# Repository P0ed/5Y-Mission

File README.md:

# 5Y-Mission
4U modular analog synthesizer

The panel contains 4 submodules with identical UI. Each unit has:  
* 8 banana jacks and 4 potentiometers laid out in a 4x3 grid  
* 2 5mm LED  
* 2 toggle switches  

### Parts:  
Potentiometer: Bourns 51AAD-B24-A20L  
Banana jack: Pomona 1581  
Switch: NKK A12HP  
Opamp: AD823  
Electronic switch: ADG419/DG419  
Multiplier: AD633  
Zener reference: ADR5045/LM4040  
Flip-flop: CD4013  
NAND: CD4093  
XOR: CD4070  
Counter: CD4029  
VCA: THAT2180  

Resistors SMT: Panasonic 0.1-1% 1206 E6  
Capacitors SMT: TDK C0G 50V 1206 E6  
Resistors THT: Vishay MBA0204 1% 0.4W E6  
Capacitors THT: TDK C0G 50V P:5mm E6  

Board connectors:  
Power: MTA156  
Signal male: 1-826629-6 female:  1-215297-6  

Case connectors:  
Power: AG4MCC  
Audio: AG3MCC  
Controls: AG5MCC  

LEMO connectors:  
FGG.0B.303.CLAD42  
EGG.0B.303.CLL  
PHG.0B.303.CLLD42  

### OSHWLab:
* [PCB panel](https://oshwlab.com/com.poed/panel-typ-i)
* [Dual modules motherboard PCB](https://oshwlab.com/com.poed/motherboard)
* [Mixer module](https://oshwlab.com/com.poed/4u-mixer)
* [Blank module PCB](https://oshwlab.com/com.poed/blank)

### Modules:
* [Voltage mixer](Modules/Mixer.md)
* [4 step sequencer](Modules/Sequencer.md)
* [Function generator](Modules/Function.md)
* AD633 multiplier

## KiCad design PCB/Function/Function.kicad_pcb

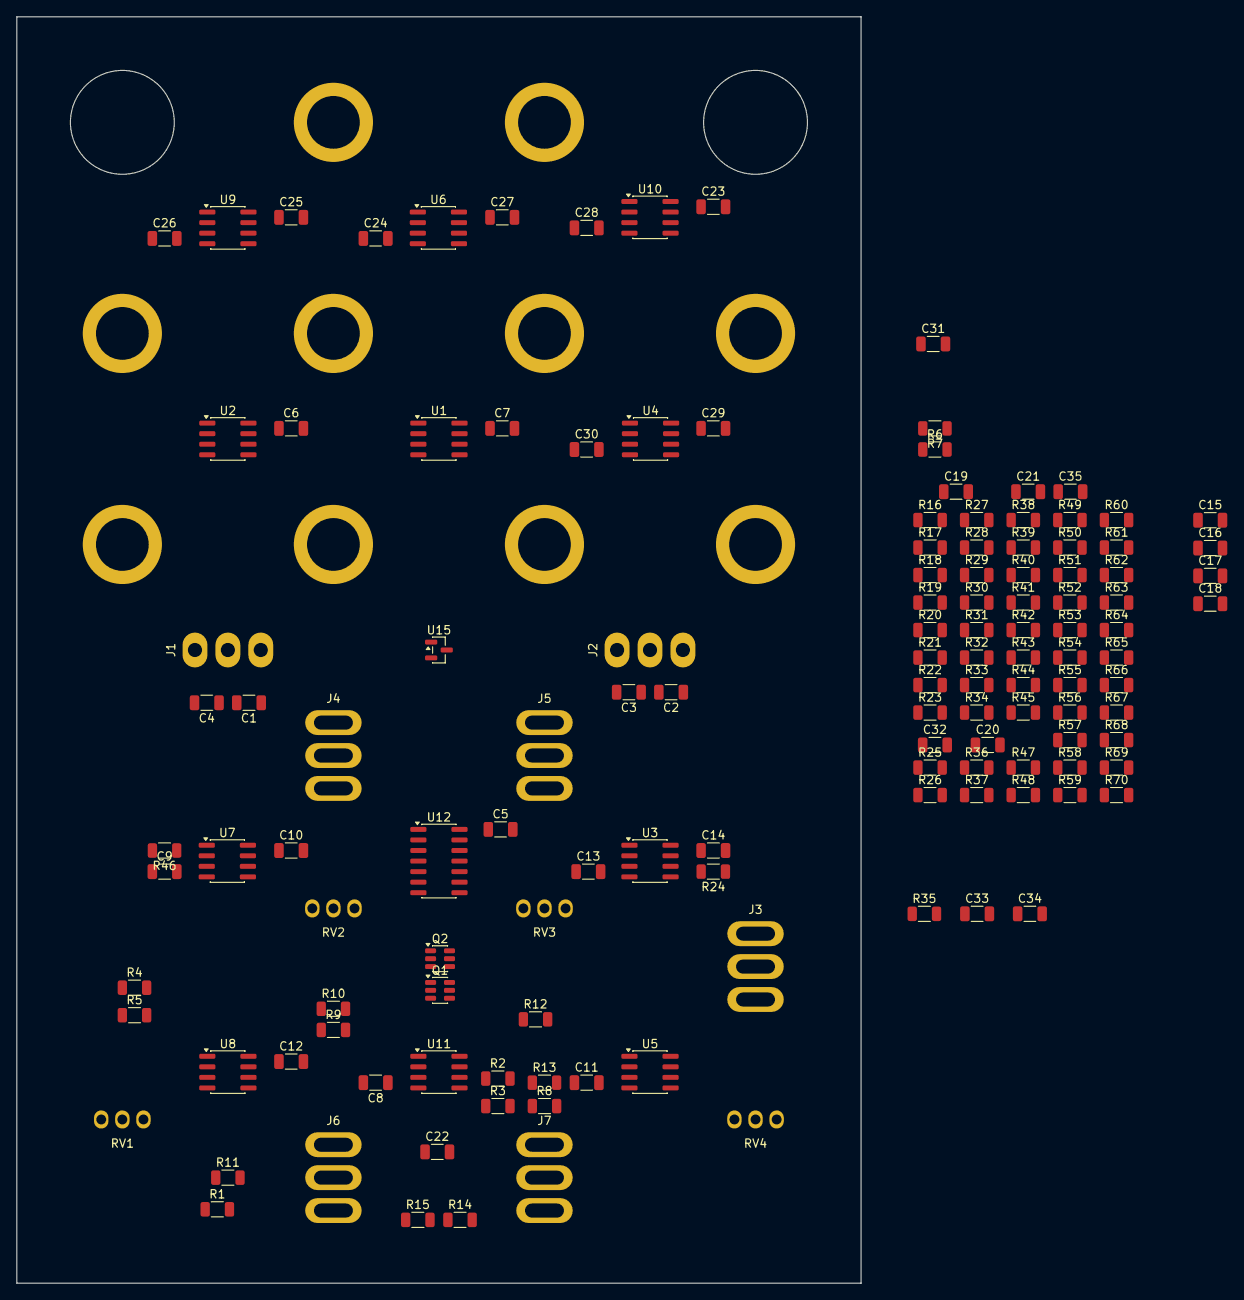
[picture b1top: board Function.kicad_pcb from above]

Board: 2 copper layers, 101.6 x 152.4 mm, 141 parts (0 on the bottom side), 75 nets, no tracks yet.

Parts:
C1, C2, C3, C4: 4u7; C_1206_3216Metric
C5, C6, C7, C8, C9, C10, C11, C12, C13, C14, C15, C16, C17, C23, C24, C25, C26, C27, C28, C29, C30: 100n; C_1206_3216Metric
C18, C19, C20, C21, C31, C32, C33, C34, C35: 47p; C_1206_3216Metric
C22: 4n7; C_1206_3216Metric
J1: MTA156-3
J2: MTA156-3-PWR; MTA156-3
J3, J4, J5: MN12; MBNF15
J6, J7: MBNF15
J**1, J**2, J**3, J**4, J**5, J**6, J**7, J**8, J**9, J**10: Pomona_1581; Pomona-1581
Q1: BC847; SOT-23-6
Q2: BCM857; SOT-23-6
R1, R12, R14, R15, R16, R47, R49: 4K7; R_1206_3216Metric
R2, R8, R56: 680K; R_1206_3216Metric
R3, R5, R45, R55: 10K; R_1206_3216Metric
R4, R6, R7, R9, R11, R22, R25, R50, R51, R52, R53, R54, R57, R58, R60, R63, R66, R69: 100K; R_1206_3216Metric
R10, R42, R44, R46, R48, R59, R61, R62, R64, R65, R67, R68, R70: 68K; R_1206_3216Metric
R13, R17, R39, R40: 150K; R_1206_3216Metric
R18: 6M8; R_1206_3216Metric
R19, R21, R24, R27, R29, R30, R31, R32, R34, R35, R36, R37: 47K; R_1206_3216Metric
R20, R28, R33, R38: 470; R_1206_3216Metric
R23, R26, R41, R43: 33K; R_1206_3216Metric
RV1, RV2, RV3, RV4: Bourns_51
U1, U2, U3, U4, U5, U6, U7, U8, U9, U10: AD823; SOIC-8
U11: ADG419; SOIC-8_3.9x4.9mm_P1.27mm
U12: 4013; SOIC-14_3.9x8.7mm_P1.27mm
U15: ADR5045; SOT-23

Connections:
ATK: R9.2, R51.2, U12.1 (Q)
DEK: R52.2, U12.13 (Q)
DRV: C31.2, R44.1, R50.1, U8.1
END: J3.1, R11.1, R22.1, U2.1
ENDO: J**2.1, R19.2, R20.1
FAB: J4.2, U10.6 (-), U10.7
FALLN: J4.1, R66.2
FALLP: J4.3, R69.2
FALL_IN: J**8.1, RV3.3
FAP: R14.1, U10.5 (+)
FB: R70.2, U10.1, U10.2 (-)
FP: RV1.2, U10.3 (+)
FREQ: J**7.1, R62.2, R68.2
GND: C1.2, C2.2, C3.1, C4.1, C5.2, C6.2, C7.2, C8.2, C9.1, C10.2, C11.1, C12.2, C13.1, C14.2, C15.1, C16.2, C17.1, C23.2, C24.1, C25.2, C26.1, C27.2, C28.1, C29.2, C30.1, J1.2, J2.2, Q1.2 (B), Q1.6 (C), Q2.2 (B), Q2.6 (C), R1.1, R4.1, R6.2, R8.1, R10.2, R17.1, R23.1, R26.1, R31.1, R34.1, R36.1, R39.1, R40.1, R42.1, R53.2, R54.2, R58.1, RV1.1, RV2.1, RV3.1, RV4.1, U1.4 (V-), U2.4 (V-), U5.5 (+), U6.3 (+), U6.5 (+), U7.3 (+), U7.5 (+), U11.3 (GND), U12.3 (C), U12.4 (R), U12.6 (S), U12.7 (VSS), U12.8 (S), U12.9 (D), U12.11 (C), U15.2 (A)
HOLD: R56.1, U8.7, U11.6
HOLD_IN: J**10.1, R54.1, R55.2
LIM: R13.1, R25.1, U2.7
LIMO: J**5.1, R27.2, R28.1
LP: C22.2, R12.2, R21.1, R24.1, R29.1, R35.1, R43.2, U1.5 (+), U2.2 (-), U5.7
LPO: J**1.1, R37.2, R38.1
NLPO: J**4.1, R32.2, R33.1
NVFF: C32.2, R46.1, R65.2, U7.1
NVRF: C35.2, Q1.5 (B), R49.1, U6.1
unnamed: C18.2, R20.2, U3.1
unnamed: C19.2, R28.2, U3.7
unnamed: C20.2, R33.2, U4.7
unnamed: C21.2, R38.2, U4.1
unnamed: R1.2, U1.6 (-)
unnamed: Q1.1 (E), Q1.4 (E), Q2.1 (E), Q2.4 (E), R45.1
unnamed: Q1.3 (C), Q2.3 (C), U11.1
unnamed: R14.2, RV3.2
unnamed: R15.2, RV4.2
unnamed: R45.2, U5.1
unnamed: R2.1, R3.2, U1.3 (+)
unnamed: R6.1, R7.2, U1.2 (-)
unnamed: R9.1, R10.1, R11.2, R18.2, U2.3 (+)
unnamed: R16.1, R17.2, U2.5 (+)
unnamed: R12.1, R13.2, U2.6 (-)
unnamed: R22.2, R23.2, R40.2, U3.3 (+)
unnamed: C18.1, R19.1, R21.2, U3.2 (-)
unnamed: R25.2, R26.2, R39.2, U3.5 (+)
unnamed: C19.1, R24.2, R27.1, U3.6 (-)
unnamed: R35.2, R36.2, U4.3 (+)
unnamed: C21.1, R34.2, R37.1, U4.2 (-)
unnamed: R30.2, R31.2, U4.5 (+)
unnamed: C20.1, R29.2, R32.1, U4.6 (-)
unnamed: R43.1, R44.2, U5.3 (+)
unnamed: R41.1, R42.2, U5.2 (-)
unnamed: C22.1, U5.6 (-), U11.2
unnamed: C35.1, R49.2, R59.1, R60.1, R61.1, U6.2 (-)
unnamed: C34.1, R48.2, R62.1, R63.1, R64.1, U6.6 (-)
unnamed: C32.1, R46.2, R66.1, R67.1, U7.2 (-)
unnamed: C33.1, R47.2, R65.1, R68.1, R69.1, R70.1, U7.6 (-)
unnamed: R52.1, R53.1, U8.3 (+)
unnamed: C31.1, R50.2, R51.1, U8.2 (-)
unnamed: R55.1, R56.2, U8.5 (+)
unnamed: R57.1, R58.2, U8.6 (-)
RAB: J5.2, U9.1, U9.2 (-)
RAP: R15.1, U9.3 (+)
RB: R64.2, U9.6 (-), U9.7
REF: J6.1, J7.1, R5.1, R7.1, R16.2, R18.1, R30.1, R57.2, R61.2, R67.2, RV1.3, RV2.3, U15.1 (K)
RISEN: J5.1, R60.2
RISEP: J5.3, R63.2
RISE_IN: J**9.1, RV4.3
RP: RV2.2, U9.5 (+)
SIGB: J6.2, R41.2
SIG_IN: J6.3, J**3.1
TRIG: R2.2, U1.1
TRIGB: J7.2, R3.1, R4.2
TRIGSW: J3.2, R8.2, U12.5 (D)
TRIG_IN: J7.3, J**6.1
VCC: C1.1, C2.1, C5.1, C6.1, C7.1, C8.1, C10.1, C12.1, C14.1, C16.1, C23.1, C25.1, C27.1, C29.1, J1.3, J2.3, J3.3, R5.2, U1.8 (V+), U2.8 (V+), U3.8 (V+), U4.8 (V+), U5.8 (V+), U6.8 (V+), U7.8 (V+), U8.8 (V+), U9.8 (V+), U10.8 (V+), U11.4 (V+), U11.5 (VL), U12.10 (R), U12.14 (VDD)
VEE: C3.2, C4.2, C9.2, C11.2, C13.2, C15.2, C17.2, C24.2, C26.2, C28.2, C30.2, J1.1, J2.1, U3.4 (V-), U4.4 (V-), U5.4 (V-), U6.4 (V-), U7.4 (V-), U8.4 (V-), U9.4 (V-), U10.4 (V-), U11.7 (V-)
VFF: C33.2, Q2.5 (B), R47.1, U7.7
VRF: C34.2, R48.1, R59.2, U6.7

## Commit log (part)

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2023-10-25 Add panel and parts datasheets
2023-10-25 Add .gitignore
2023-10-25 Update function
2023-11-02 Add mixer
2023-11-02 Update mixer
2023-11-03 Add hold to function
2024-02-20 Add 1900 knob clone
2024-02-21 Update module
2024-03-24 Update simulations and parts list
2024-05-20 Add motherboard
2024-06-29 Update case and spacers
2024-06-29 Update sequencer
2024-09-05 Update function design
2024-10-17 Add tricoder
2025-03-02 Add tricorder
2025-03-08 Add program compiler tokenizer
2025-03-08 Fix warning
2025-03-09 Update Termial UI
2025-03-10 Update tokenizer
2025-03-10 Add Scope
2025-03-19 Update Scope
2025-03-26 Add breakpoint
2025-03-27 Add debugger
2025-03-28 Update colors
2025-03-28 Add more colors
2025-04-04 Add VIBES.md
2025-04-05 Update vibes
2025-04-05 Update tests
2025-04-05 Update Program
2025-04-06 Add .clineignore
2025-04-06 Add more tests
2025-04-06 Add SUB, DIV, MOD instructions
2025-04-06 Fix complex expressions
2025-04-06 Fix strings
2025-04-06 Update grammar
2025-04-07 Update module 3d model
2025-04-08 Add precompiler and recursive expr mutations
2025-04-08 Move hex string function
2025-04-08 Save debug mode to user defaults
2025-04-09 Update binary expr representation
2025-04-09 Update viebes
2025-04-09 Add TASKS.md
2025-04-09 Update rules
2025-04-09 Update VM
2025-04-09 Fix captures
2025-04-09 Add basic closures
2025-04-09 Fix traverse
2025-04-09 Add leavesFirst
2025-04-09 Add Arrow
2025-04-09 WIP type inference
2025-04-10 Fix closure capture offset Update Parser Add simple composition Update lambda type inference
2025-04-10 Update tuple description
2025-04-11 Add () function calls
2025-04-13 Fix Socpe.root
2025-07-29 Add NPN-Slope
2025-07-29 Add NPN slopes
2025-07-29 Update NPN slope
2025-07-31 Add VCA
2025-07-31 Update VCA
2026-02-26 Add Fn.asc
2026-02-28 Update Fn.asc add Schmitt triggers to comparators
2026-03-01 Add flip-flop, END, LIM
2026-03-02 Update simulation
2026-03-04 Update Function schematic
2026-03-04 Start placement
2026-03-04 Compactify schematics
